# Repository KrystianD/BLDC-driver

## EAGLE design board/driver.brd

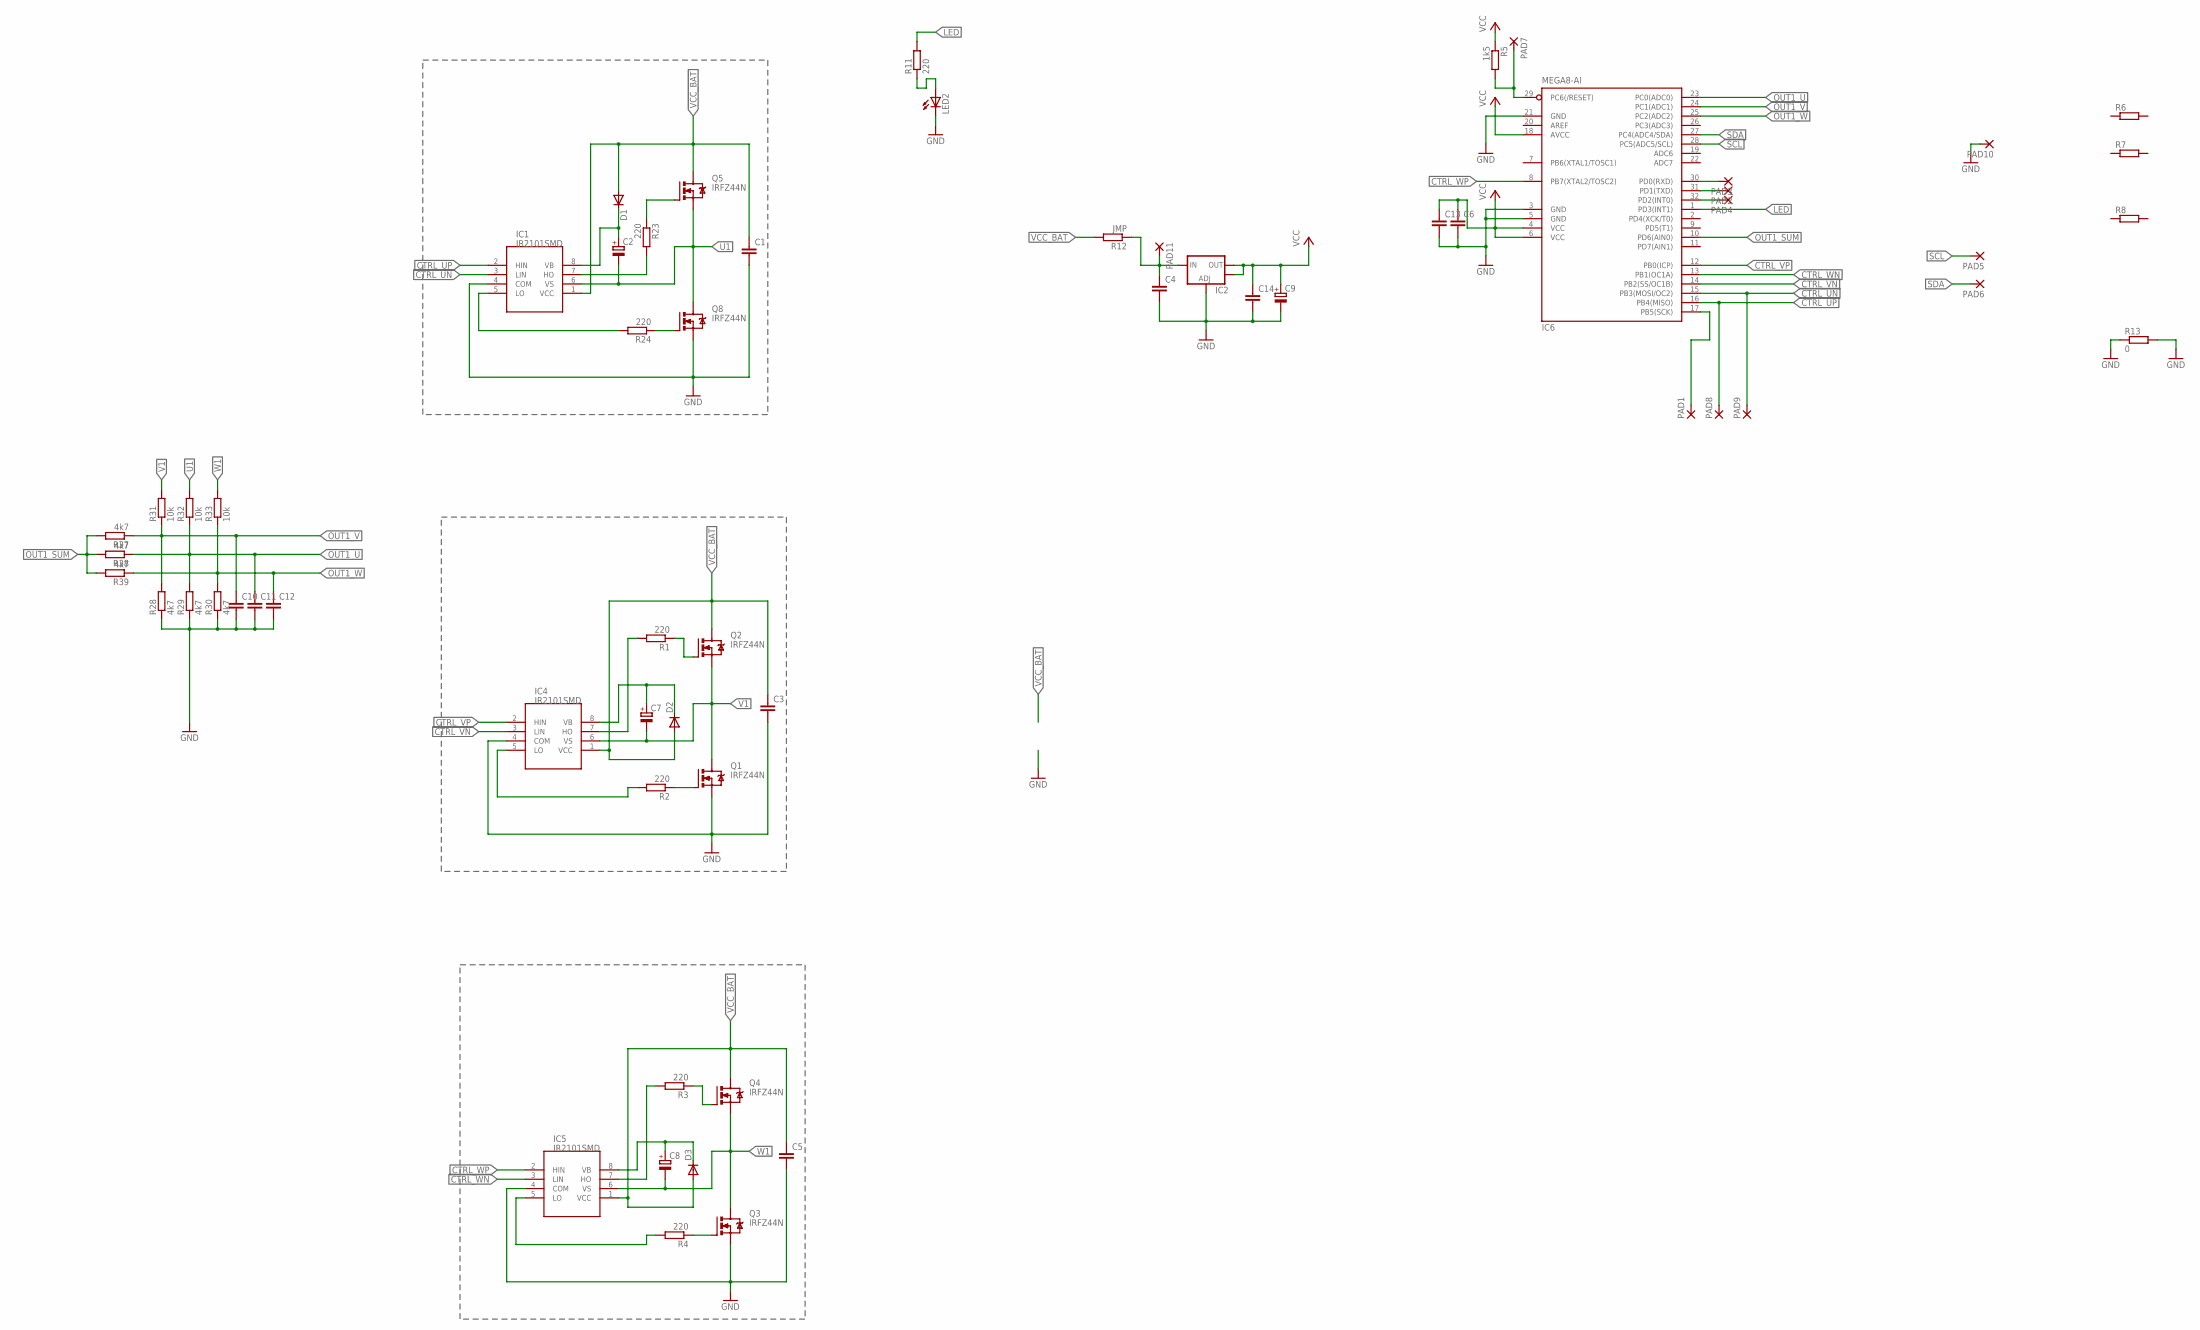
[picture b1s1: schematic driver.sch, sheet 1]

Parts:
C1, C3, C4, C5, C6, C10, C13, C14: C-EUC0805; C0805
C2, C7, C8, C9: CPOL-EUSANYO_SMD_A5; SANYO-OSCON_SMD_A5
C11, C12: C-EUC1206; C1206
D1, D2, D3: DIODE-MINIMELF; MINIMELF
IC1, IC4, IC5: IR2101SMD; SO08
IC2: V_REG_LM1117SOT223; SOT223
IC6: MEGA8-AI; TQFP32-08
LED2: LEDCHIPLED_0805; CHIPLED_0805
PAD1, PAD2, PAD3, PAD4, PAD7, PAD8, PAD9: SMD2; SMD1,27-2,54
PAD5, PAD6, PAD10, PAD11: SMD5; SMD2,54-5,08
Q1, Q2, Q3, Q4, Q5, Q8: IRFZ44N; TO220BH-FILL
R1, R2, R3, R4, R23, R24: 220; R1206
R5: 1k5; R1206
R6, R7, R8: R-EU_R1206; R1206
R11: 220; R0805
R12: JMP; R0805
R13: 0; R1206
R28, R37, R38: 4k7; R0805
R29, R30, R39: 4k7; R1206
R31: 10k; R0805
R32, R33: 10k; R1206

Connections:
CTRL_UN: IC1.3 (LIN), IC6.15 (PB3(MOSI/OC2)), PAD9.1
CTRL_UP: IC1.2 (HIN), IC6.16 (PB4(MISO)), PAD8.1
CTRL_VN: IC4.3 (LIN), IC6.14 (PB2(SS/OC1B))
CTRL_VP: IC4.2 (HIN), IC6.12 (PB0(ICP))
CTRL_WN: IC5.3 (LIN), IC6.13 (PB1(OC1A))
CTRL_WP: IC5.2 (HIN), IC6.8 (PB7(XTAL2/TOSC2))
GND: C1.2, C3.2, C4.2, C5.2, C6.2, C9.-, C10.2, C11.2, C12.2, C13.2, C14.2, IC1.4 (COM), IC2.1 (ADJ), IC4.4 (COM), IC5.4 (COM), IC6.3 (GND), IC6.5 (GND), IC6.21 (GND), LED2.C, PAD10.1, Q1.S, Q3.S, Q8.S, R13.1, R13.2, R28.1, R29.1, R30.1
LED: IC6.1 (PD3(INT1)), R11.2
unnamed: IC1.5 (LO), R24.2
unnamed: IC1.7 (HO), R23.2
unnamed: Q2.G, R1.1
unnamed: Q1.G, R2.1
unnamed: C2.+, D1.C, IC1.8 (VB)
unnamed: IC4.5 (LO), R2.2
unnamed: IC4.7 (HO), R1.2
unnamed: C7.+, D2.C, IC4.8 (VB)
unnamed: Q4.G, R3.1
unnamed: Q3.G, R4.1
unnamed: IC5.5 (LO), R4.2
unnamed: IC5.7 (HO), R3.2
unnamed: C8.+, D3.C, IC5.8 (VB)
unnamed: IC6.29 (PC6(/RESET)), PAD7.1, R5.2
unnamed: IC6.17 (PB5(SCK)), PAD1.1
unnamed: IC6.30 (PD0(RXD)), PAD3.1
unnamed: IC6.31 (PD1(TXD)), PAD2.1
unnamed: IC6.32 (PD2(INT0)), PAD4.1
unnamed: Q5.G, R23.1
unnamed: Q8.G, R24.1
unnamed: LED2.A, R11.1
unnamed: C4.1, IC2.3 (IN), PAD11.1, R12.1
OUT1_SUM: IC6.10 (PD6(AIN0)), R37.2, R38.2, R39.2
OUT1_U: C11.1, IC6.23 (PC0(ADC0)), R29.2, R32.1, R38.1
OUT1_V: C10.1, IC6.24 (PC1(ADC1)), R28.2, R31.1, R37.1
OUT1_W: C12.1, IC6.25 (PC2(ADC2)), R30.2, R33.1, R39.1
SCL: IC6.28 (PC5(ADC5/SCL)), PAD5.1
SDA: IC6.27 (PC4(ADC4/SDA)), PAD6.1
U1: C2.-, IC1.6 (VS), Q5.S, Q8.D, R32.2
V1: C7.-, IC4.6 (VS), Q1.D, Q2.S, R31.2
VCC: C6.1, C9.+, C13.1, C14.1, IC2.2 (OUT), IC2.4 (OUT), IC6.4 (VCC), IC6.6 (VCC), IC6.18 (AVCC), R5.1
VCC_BAT: C1.1, C3.1, C5.1, D1.A, D2.A, D3.A, IC1.1 (VCC), IC4.1 (VCC), IC5.1 (VCC), Q2.D, Q4.D, Q5.D, R12.2
W1: C8.-, IC5.6 (VS), Q3.D, Q4.S, R33.2

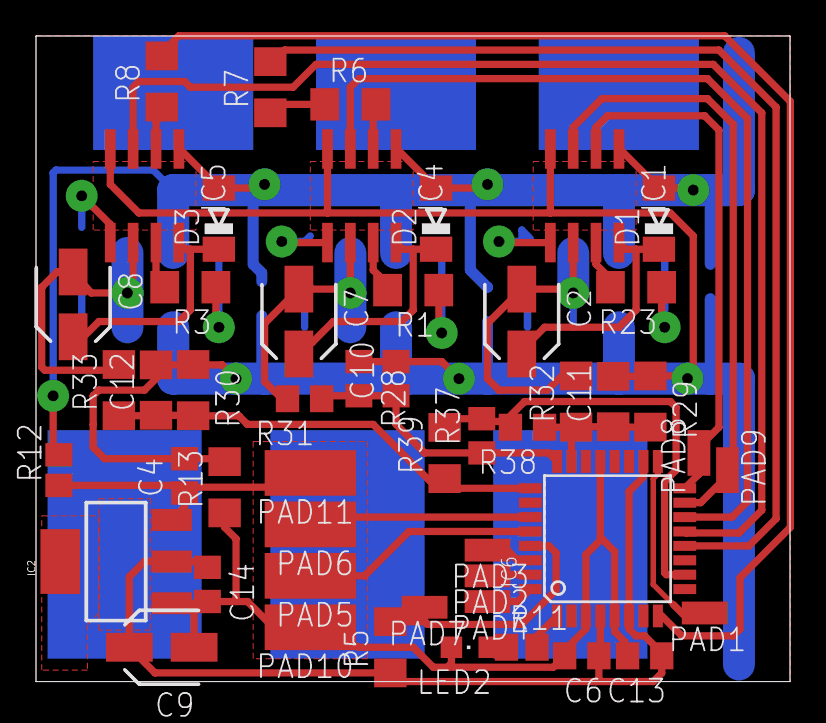
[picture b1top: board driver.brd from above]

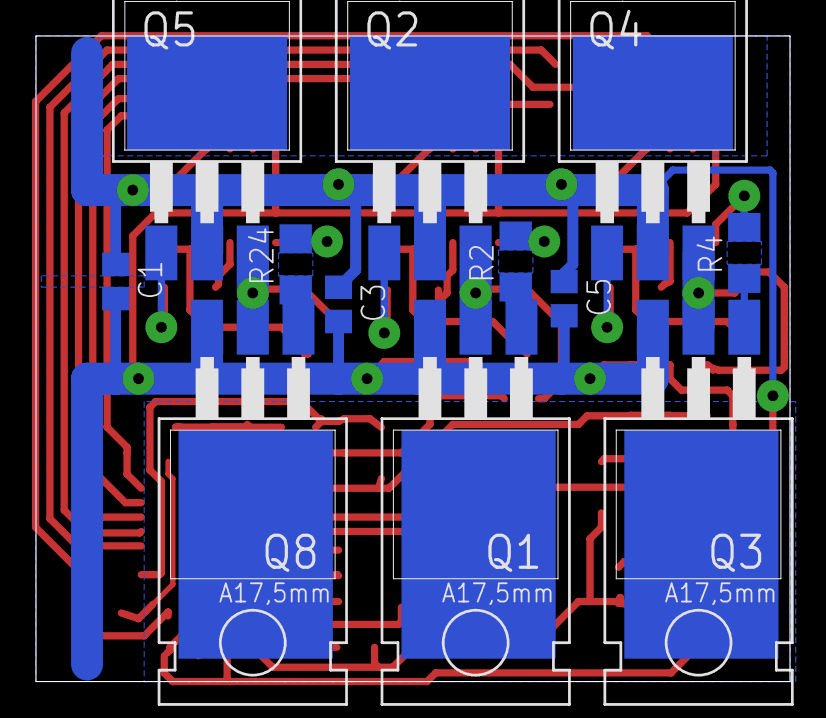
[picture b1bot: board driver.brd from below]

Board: 2 copper layers, 41.9 x 35.9 mm, 62 parts (12 on the bottom side), 41 nets.

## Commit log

2014-05-14 adjusted hardware definitons
2014-05-15 added device id recognizing
2014-05-24 added support for general call duty factor is now obtained from proper byte
2014-05-24 huge performance optimization in phases switching
2014-05-24 moved phases definition to another file
2014-05-24 removed read-modify-write operation from phases switching function
2014-05-24 added definitions for reverse direction
2014-05-25 moved bldc code from main to its own module added desired duty cycle added managing motor states added starting motor times and times generator
2014-05-25 added script for resetting device
2014-05-25 performing crc calculation as soon as byte arrives
2014-05-25 fixed motor starting phase
2014-05-25 some code optimizations enabled
2014-05-25 added settings command for setting startup duty and direction more optimization in phases switching (register variables) added variable length packets
2014-05-25 added python library
2014-05-26 fixed possible race condition
2014-05-26 added reset command to the library
2014-05-26 changed wrapper for i2c connection added broadcast to set_duty app
2014-05-26 definitions moved to another file
2014-05-27 removed unneded code from interrupt handler
2014-05-27 merged commands CMD_STATUS and CMD_DUTY got rid of comm_state variable
2014-05-27 extracted STABILIZATION state from sequential startup stage
2014-05-27 reorganized project structure added python library added simple C++ program
2014-05-27 restored CMD_STATUS command added i2c write-read functionality to py library added tool for reading motor status
2014-05-27 added .gitignore files
2014-06-28 added board and schematic
2014-08-17 added Makefile and avr-utils project
2014-08-17 refactor
2014-08-17 fixed debug module removed custom config.cfg
2020-04-19 added photo and license
2023-04-01 makefile fixes
2023-04-13 typo

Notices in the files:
parts and their libraries:
SparkFun: Licensing: CC v3.0 Share-Alike You are welcome to use this library for commercial purposes.
